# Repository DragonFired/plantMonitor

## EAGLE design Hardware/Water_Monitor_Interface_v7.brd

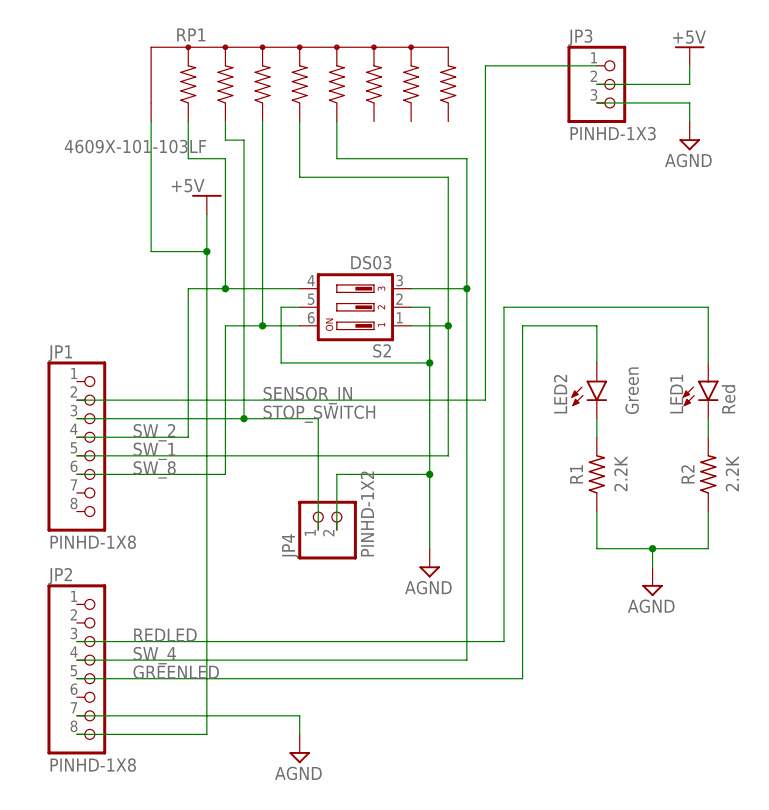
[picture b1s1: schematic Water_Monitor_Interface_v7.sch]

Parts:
JP1, JP2: PINHD-1X8; 1X08
JP3: PINHD-1X3; 1X03
JP4: PINHD-1X2; 1X02
LED1: Red; LED3MM
LED2: Green; LED_3MM-NS
R1, R2: 2.2K; RESAD724W46L381D178B
RP1: 4609X-101-103LF
S2: DS03; DS-03

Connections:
+5V: JP2.8, JP3.2, RP1.1
AGND: JP2.7, JP3.3, JP4.2, R1.1, R2.1, S2.2, S2.5
GREENLED: JP2.5, LED2.A
unnamed: LED1.K (C), R2.2
unnamed: LED2.K (C), R1.2
REDLED: JP2.3, LED1.A
SENSOR_IN: JP1.2, JP3.1
STOP_SWITCH: JP1.3, JP4.1, RP1.3
SW_1: JP1.5, RP1.5, S2.1
SW_2: JP1.4, RP1.2, S2.4
SW_4: JP2.4, RP1.6, S2.3
SW_8: JP1.6, RP1.4, S2.6

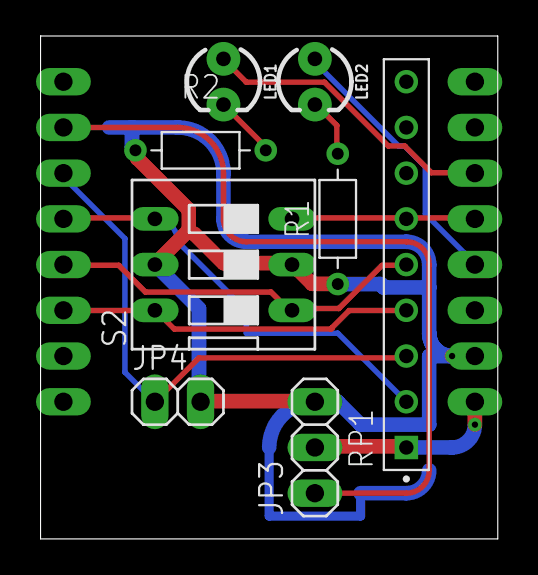
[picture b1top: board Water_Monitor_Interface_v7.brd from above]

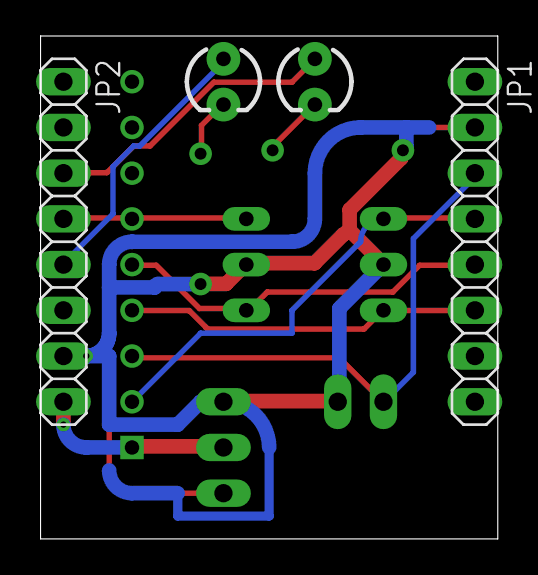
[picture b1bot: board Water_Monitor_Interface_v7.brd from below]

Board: 2 copper layers, 25.4 x 27.9 mm, 10 parts (2 on the bottom side), 12 nets.

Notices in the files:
parts and their libraries:
SparkFun-LED: Licensing: Creative Commons ShareAlike 4.0 International - https://creativecommons.org/licenses/by-sa/4.0
